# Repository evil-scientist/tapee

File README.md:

# tapee

tapee is a small internet-connected robot that prints short snippets on thermal paper. A Raspberry Pi Zero drives a 58 mm TTL receipt printer. Press the button on top and it prints a slip.

The print format is still being designed. For now, a button press prints a placeholder ticket with the date and time.

## Hardware

- Raspberry Pi Zero W or Zero 2 W, with header pins
- The tapee HAT (in `pcb/`), which stacks on the Pi
- TTL thermal printer, DP-EH500 / CSN-A2 type (Adafruit-compatible, 384 dots wide, 9600 baud)
- 5 V USB-C supply for the Pi, and a 5 V 2 A supply for the printer
- Momentary push button
- microSD card, 8 GB or larger
- The printed robot body (in `cad/robot/`)

## Connecting the HAT

| HAT connector | Connects to |
| --- | --- |
| J4, USB-C | 5 V supply for the Pi. It feeds the Pi through an ideal diode. |
| J5, screw terminal (PRINTER 5V) | 5 V 2 A supply for the printer. |
| J2, JST-XH 5-pin (PRINTER) | The printer's TTL cable: GND, RX, TX, DTR, VH. |
| J3, 2-pin header (BUTTON) | The push button. |

The printer can draw close to 2 A on dark lines, so by default it has its own supply on J5. To run everything from the USB-C supply instead, close the JP1 solder bridge (USB»PRN) with a blob of solder and use a 5 V 3 A supply.

## Setup

1. Flash **Raspberry Pi OS Lite (32-bit)**. Either:
   - use Raspberry Pi Imager: in the customisation step, set the hostname to `tapee`, create a user, enter your Wi-Fi details, set your time zone, and turn on SSH; or
   - on Linux, without Imager: copy `pi/sdcard/flash.env.example` to `pi/sdcard/flash.env`, fill it in, download the image from [raspberrypi.com](https://www.raspberrypi.com/software/operating-systems/), and run:

     ```sh
     sudo bash pi/sdcard/flash.sh /dev/sdX 2026-10-06-raspios-trixie-armhf-lite.img.xz
     ```

     It refuses non-removable disks, asks you to type the device name before writing, writes the image with `dd`, and then adds the same first-boot settings Imager would. It also takes the serial console off the GPIO pins.
2. Boot the Pi and copy the files to it:

   ```sh
   ssh sury@tapee.local mkdir -p tapee
   scp -p pi/tapee.py pi/tapee.service pi/setup.sh pi/tests/test_printer.py sury@tapee.local:tapee/
   ```

3. On the Pi, run the setup script and reboot:

   ```sh
   cd ~/tapee
   sudo bash setup.sh
   sudo reboot
   ```

   The script installs `python3-serial` and `python3-gpiozero`, turns on the serial port on GPIO 14/15, moves the serial console and Bluetooth off it, and installs `tapee.service` so the button listener starts at boot.

4. Test it:

   ```sh
   python3 ~/tapee/test_printer.py --port /dev/serial0   # prints a test page
   journalctl -u tapee -f                                 # watch the button service
   ```

## Using it

- **Press** the button to print.
- **Hold** it for 5 seconds to shut the Pi down. Unplug it once the green LED stops flashing.

## Repository layout

| Path | What it is |
| --- | --- |
| `pi/` | Runs on the Pi. `tapee.py` is the button listener: it prints a ticket on a press and shuts down on a long hold. `tapee.service` is its systemd unit template, and `setup.sh` is the one-time setup. |
| `pi/sdcard/` | `flash.sh` writes the SD card with `dd` (Linux, no Imager needed); `firstboot.py` writes the cloud-init user, Wi-Fi and SSH settings onto it, from `flash.env`. |
| `pi/tests/` | `test_printer.py` prints a test page (text styles, character set, darkness check); `test_codes.py` prints barcodes and QR codes (needs `segno`). |
| `pcb/` | KiCad 10 project for the tapee HAT, a Pi Zero HAT with USB-C power, the printer connector and the button header. `tapee_hat_render.png` shows both sides. |
| `pcb/lib/` | Project footprint library: the TYPE-C 6P USB-C receptacle (LCSC C456012) and its 3D model. |
| `pcb/art/` | Scripts that generate the silkscreen labels and artwork, and `render.sh`, which redraws `pcb/tapee_hat_render.png` from the board. |
| `cad/robot/` | The printable robot body: CadQuery model, STEP assembly, one STL per part (`stl/`) and renders (`images/`). See its README. |
| `cad/printer/` | Measured CAD model of the DP-EH500 printer, used by the robot model. |
| `cad/render.py` | Renders the robot images from the parts the model writes to `cad/robot/render/`. |

The test scripts default to `/dev/ttyUSB0` for a USB-TTL adapter on a laptop. Pass `--port /dev/serial0` on the Pi.

## Ordering the HAT

The board is 2 layers, 65 × 30 mm. DRC shows no errors and no unconnected items. The 40 warnings are footprint-vs-library differences, empty description fields and the screw-terminal silkscreen at the board edge.

Fabrication outputs are not kept in git. Export them from the saved board into `pcb/fab/` (git ignores it), for example with Konnect's `export_manufacturing_package` for JLCPCB, and zip the Gerber and drill files.

- **PCB:** upload `tapee_hat-gerbers.zip`. Pick black solder mask; the silkscreen is drawn for the yellow look.
- **Assembly (optional):** upload `BOM-tapee_hat.csv` and `CPL-tapee_hat.csv`. Every symbol carries an `LCSC` field, so export the BOM with an LCSC column and JLCPCB matches the parts itself. The resistors, the 10 µF and 22 µF capacitors and the TVS diodes are Basic or Preferred parts; U1, C1 and the connectors are Extended (JLCPCB has no Basic connectors). JP1 is a solder bridge, not a part, and it and the mounting holes are marked do-not-place. Check stock in the BOM tool, and check every part's rotation in the placement preview before you order. J1, the 2×20 socket, sits on the bottom.

## Troubleshooting

- **Nothing prints:** check that the printer has power on J5 (or that JP1 is bridged), and that its cable is in J2 the right way round (GND, RX, TX, DTR, VH).
- **Random characters:** the baud rate is wrong. Hold the printer's feed button while you power it on to print a self-test page that shows the baud rate, then pass `--baud`.
- **Garbage at every boot:** the serial console is still on. Run `sudo raspi-config nonint do_serial_cons 1` and reboot.

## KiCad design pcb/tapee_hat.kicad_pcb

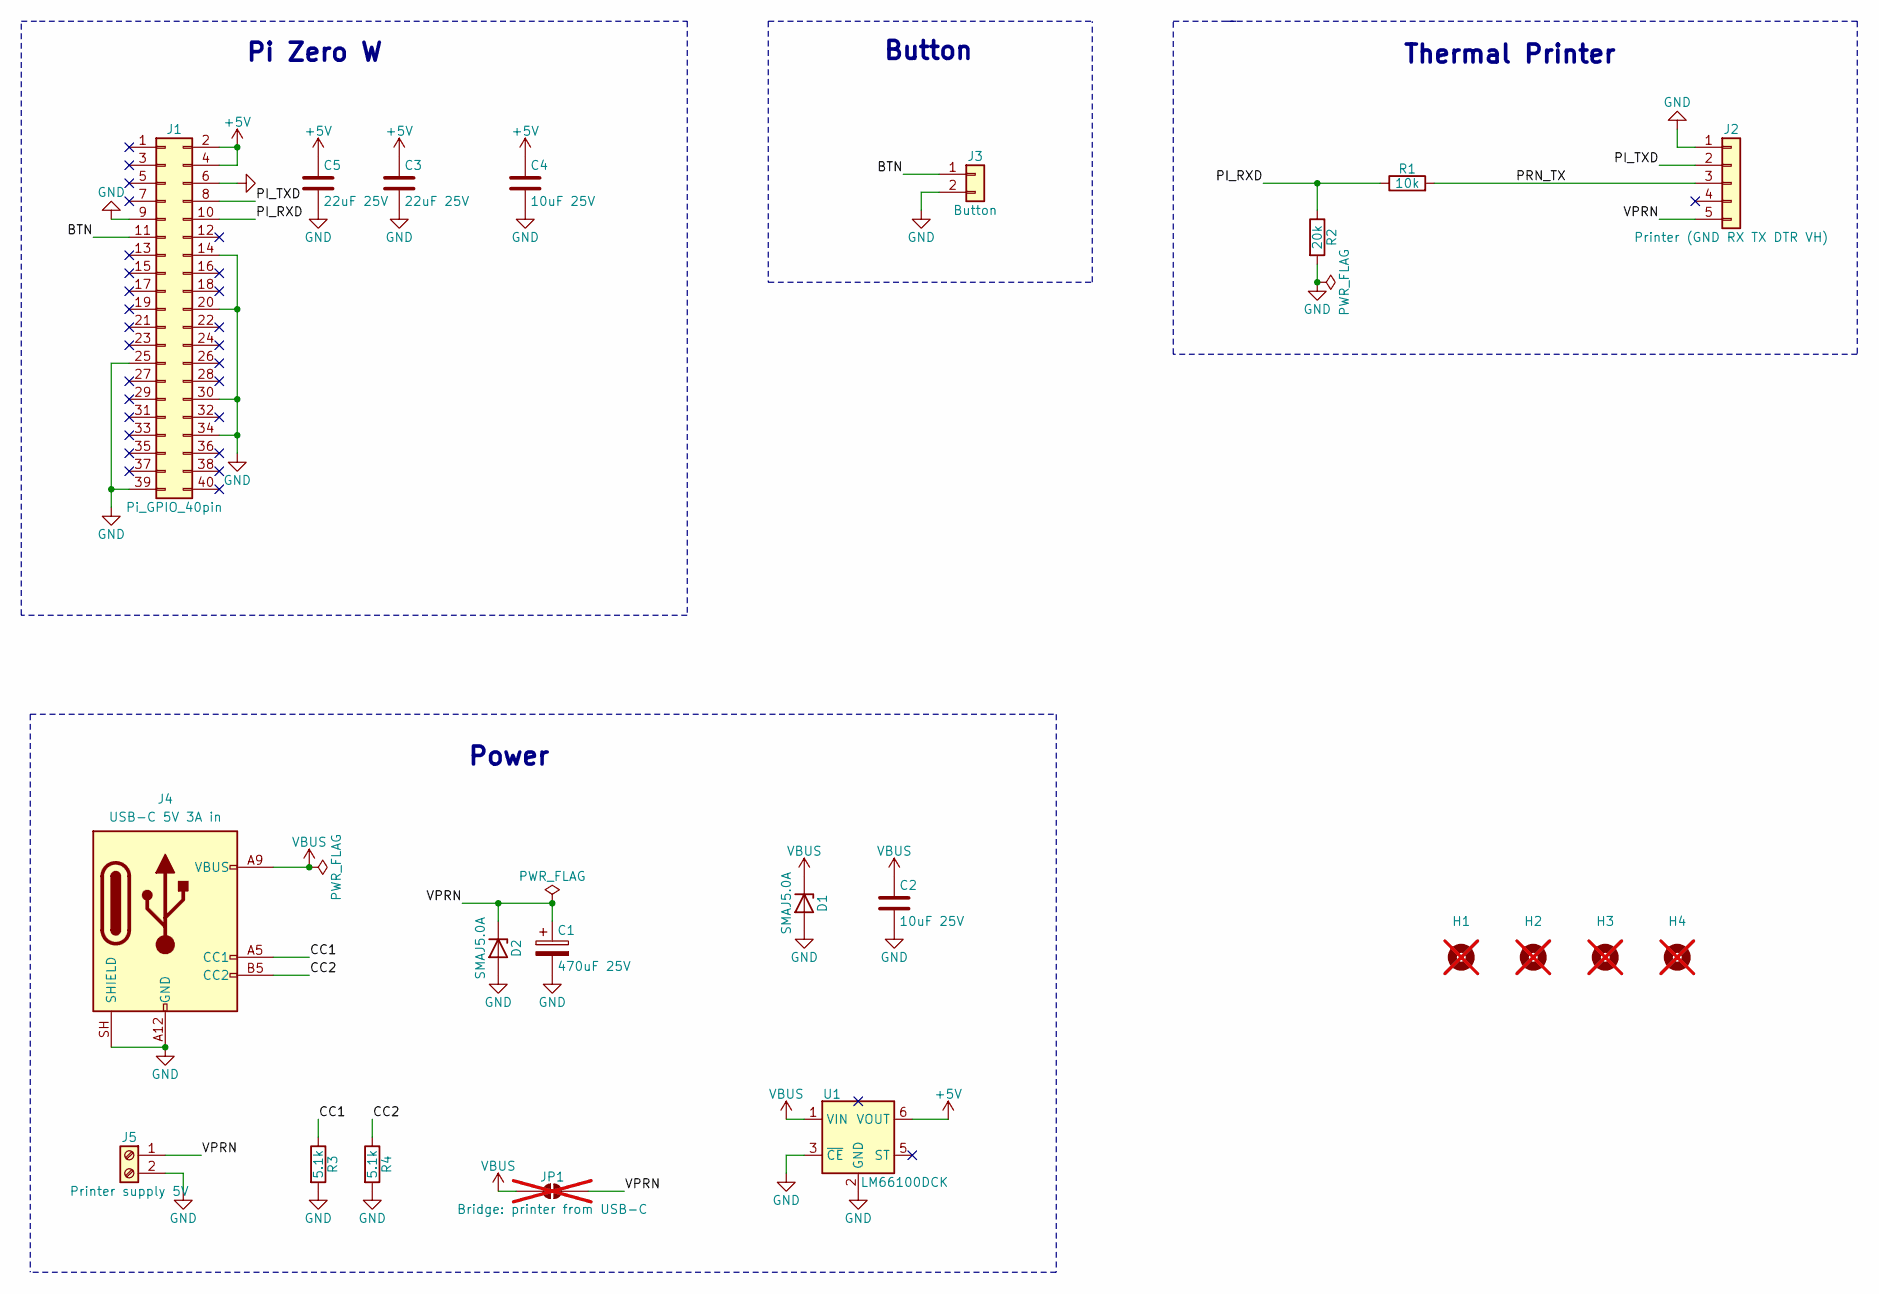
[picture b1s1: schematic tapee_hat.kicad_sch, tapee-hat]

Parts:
C1: 470uF 25V; CP_Elec_8x10; MPN RVT25V470M8X10; LCSC C47023111
C2, C4: 10uF 25V; C_0805_2012Metric; MPN CL21A106KAYNNNE; LCSC C15850
C3, C5: 22uF 25V; C_1206_3216Metric; MPN CL31A226KAHNNNE; LCSC C12891
D1, D2: SMAJ5.0A; D_SMA; MPN SMAJ5.0A; LCSC C2925443
H1, H2, H3, H4: MountingHole; MountingHole_2.7mm_M2.5; not fitted
J1: Pi_GPIO_40pin; PinSocket_2x20_P2.54mm_Vertical; MPN 2.54-2*20; LCSC C2977589
J2: Printer (GND RX TX DTR VH); JST_XH_B5B-XH-A_1x05_P2.50mm_Vertical; MPN B5B-XH-A(LF)(SN); LCSC C157991
J3: Button; PinHeader_1x02_P2.54mm_Vertical; MPN PZ254V-11-02P; LCSC C492401
J4: USB-C 5V 3A in; USB_C_TYPE-C-6P_C456012; MPN TYPE-C 6P; LCSC C456012
J5: Printer supply 5V; TerminalBlock_Phoenix_MKDS-1,5-2-5.08_1x02_P5.08mm_Horizont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; MPN MKDS 1,5/ 2-5,08; LCSC C5183929
JP1: Bridge: printer from USB-C; SolderJumper-2_P1.3mm_Open_Pad1.0x1.5mm; not fitted
R1: 10k; R_0805_2012Metric; MPN 0805W8F1002T5E; LCSC C17414
R2: 20k; R_0805_2012Metric; MPN 0805W8F2002T5E; LCSC C4328
R3, R4: 5.1k; R_0805_2012Metric; MPN 0805W8F5101T5E; LCSC C27834
U1: LM66100DCK; SOT-363_SC-70-6; MPN LM66100DCKR; LCSC C2869734

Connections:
+5V: C3.1, C4.1, C5.1, J1.2, J1.4, U1.6 (VOUT)
/BTN: J1.11, J3.1
/CC1: J4.A5 (CC1), R3.1
/CC2: J4.B5 (CC2), R4.1
/PI_RXD: J1.10, R1.1, R2.1
/PI_TXD: J1.8, J2.2
/PRN_TX: J2.3, R1.2
/VPRN: C1.1, D2.1 (K), J2.5, J5.1, JP1.2 (B)
GND: C1.2, C2.2, C3.2, C4.2, C5.2, D1.2 (A), D2.2 (A), J1.6, J1.9, J1.14, J1.20, J1.25, J1.30, J1.34, J1.39, J2.1, J3.2, J4.A12 (GND), J4.B12 (GND), J4.SH (SHIELD), J5.2, R2.2, R3.2, R4.2, U1.2 (GND), U1.3 (~CE)
VBUS: C2.1, D1.1 (K), J4.A9 (VBUS), J4.B9 (VBUS), JP1.1 (A), U1.1 (VIN)

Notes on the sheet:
Power
Pi Zero W
Button
Thermal Printer

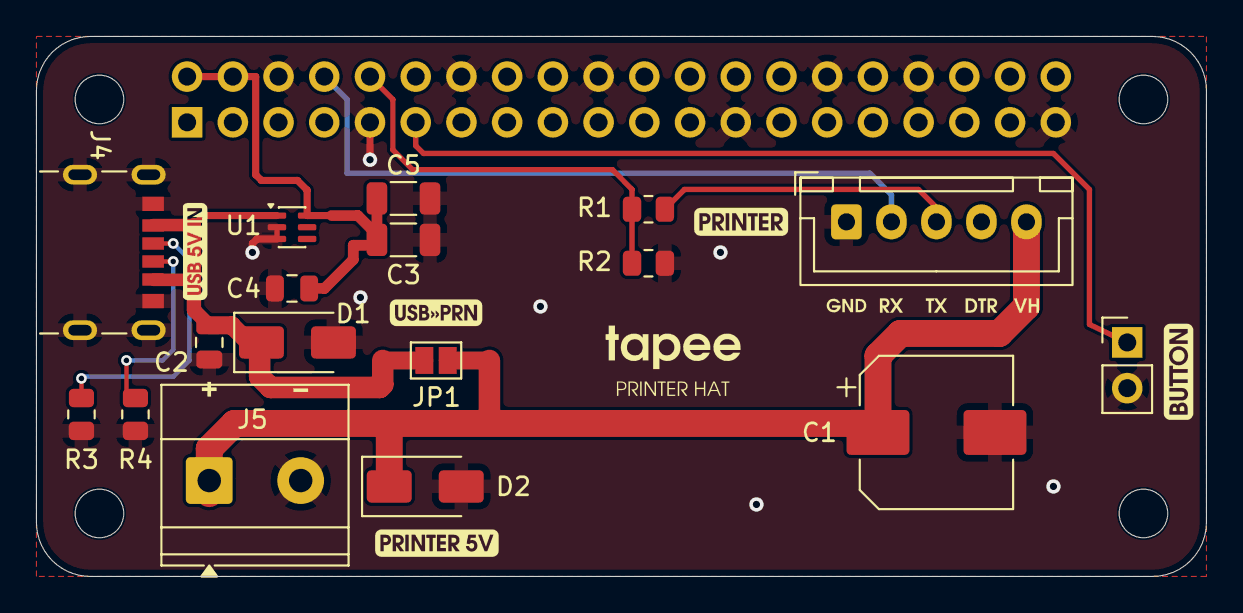
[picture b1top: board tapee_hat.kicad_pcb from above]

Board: 2 copper layers, 65.0 x 30.0 mm, 22 parts (1 on the bottom side), 10 nets.
